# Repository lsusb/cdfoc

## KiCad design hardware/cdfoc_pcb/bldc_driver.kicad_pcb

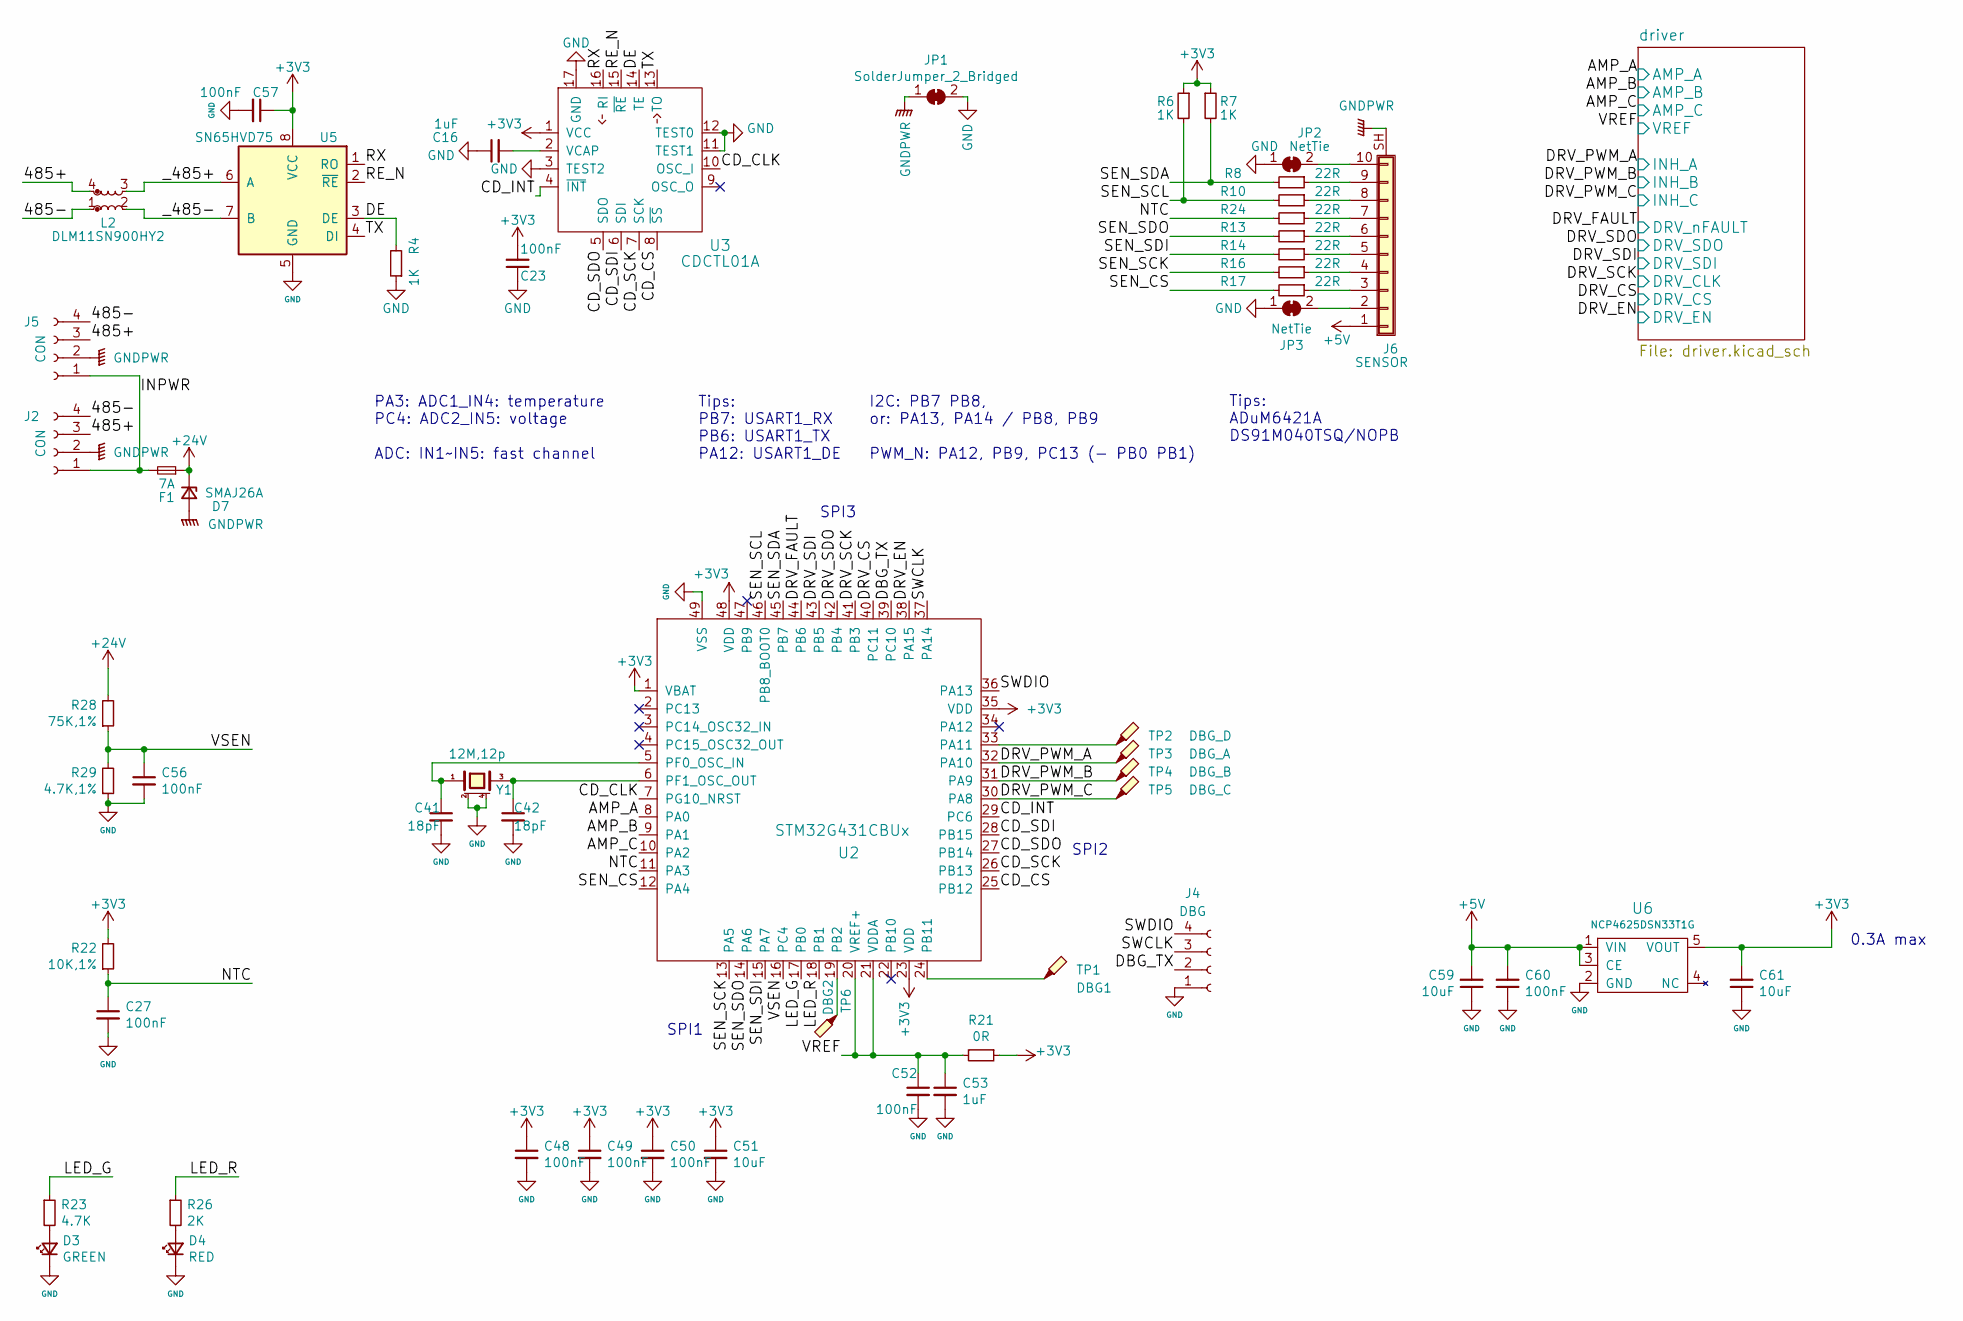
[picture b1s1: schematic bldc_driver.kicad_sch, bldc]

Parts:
C16: 1uF; 0402C_BIG
C23, C27, C48, C49, C50, C52, C56, C57, C60: 100nF; 0402
C41, C42: 18pF; 0402
C51, C59, C61: 10uF; 0402C_BIG
C53: 1uF; 0402
D3: GREEN; 0402D
D4: RED; 0402D
D7: SMAJ26A; SMA
F1: 7A; 1206R
J2, J5: CON; CONN_5268-04A_1x04_P2.50mm_H
J4: DBG; PAD_DIP_4P_1mm
J6: SENSOR; CONN_SH1.0mm_10P_HSMD
JP1: SolderJumper_2_Bridged; NetTie-2_SMD_Pad1mm
JP2, JP3: NetTie; NetTie-2_SMD_Pad0.5mm
L2: DLM11SN900HY2; L_CommonModeChoke_Coilcraft_0603USB
R4, R6, R7: 1K; 0402
R8, R10, R13, R14, R16, R17, R24: 22R; 0402
R21: 0R; 0402
R22: 10K,1%; 0402
R23: 4.7K; 0402
R26: 2K; 0402
R28: 75K,1%; 0402
R29: 4.7K,1%; 0402
TP1: DBG1; TP-D0.8mm
TP2: DBG_D; TP-D0.8mm
TP3: DBG_A; TP-D0.8mm
TP4: DBG_B; TP-D0.8mm
TP5: DBG_C; TP-D0.8mm
TP6: DBG2; TP-D0.8mm
U2: STM32G431CBUx; QFN-48-1EP_7x7mm_P0.5mm_EP5.6x5.6mm
U3: CDCTL01A; QFN-16-1EP_3x3mm_P0.5mm_EP1.7x1.7mm
U5: SN65HVD75; SON-8
U6: NCP4625DSN33T1G; SOT-23-5
Y1: 12M,12p; XTAL-3225

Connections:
+3V3: C23.2, C48.1, C49.1, C50.1, C51.1, C57.1, C61.2, R6.1, R7.1, R21.1, R22.2, U2.1 (VBAT), U2.23 (VDD), U2.35 (VDD), U2.48 (VDD), U3.1 (VCC), U5.8 (VCC), U6.5 (VOUT); also elsewhere on the board
+5V: C59.2, C60.2, J6.1, U6.1 (VIN), U6.3 (CE); also elsewhere on the board
+24V: D7.1 (K), F1.1, R28.2; also elsewhere on the board
/485+: J2.3, J5.3, L2.4
/485-: J2.4, J5.4, L2.1
/AMP_A: U2.8 (PA0); also elsewhere on the board
/AMP_B: U2.9 (PA1); also elsewhere on the board
/AMP_C: U2.10 (PA2); also elsewhere on the board
/CD_CLK: U2.7 (PG10_NRST), U3.10 (OSC_I)
/CD_CS: U2.25 (PB12), U3.8 (~SS)
/CD_INT: U2.29 (PC6), U3.4 (~INT)
/CD_SCK: U2.26 (PB13), U3.7 (SCK)
/CD_SDI: U2.28 (PB15), U3.6 (SDI)
/CD_SDO: U2.27 (PB14), U3.5 (SDO)
/DBG_TX: J4.2, U2.39 (PC10)
/DE: R4.2, U3.14 (TE), U5.3 (DE)
/DRV_CS: U2.40 (PC11); also elsewhere on the board
/DRV_EN: U2.38 (PA15); also elsewhere on the board
/DRV_FAULT: U2.44 (PB6); also elsewhere on the board
/DRV_PWM_A: TP3.1, U2.32 (PA10); also elsewhere on the board
/DRV_PWM_B: TP4.1, U2.31 (PA9); also elsewhere on the board
/DRV_PWM_C: TP5.1, U2.30 (PA8); also elsewhere on the board
/DRV_SCK: U2.41 (PB3); also elsewhere on the board
/DRV_SDI: U2.43 (PB5); also elsewhere on the board
/DRV_SDO: U2.42 (PB4); also elsewhere on the board
/INPWR: F1.2, J2.1, J5.1
/LED_G: R23.1, U2.17 (PB0)
/LED_R: R26.1, U2.18 (PB1)
/NTC: C27.1, R22.1, R24.2, U2.11 (PA3)
/RE_N: U3.15 (~RE), U5.2 (~RE)
/RX: U3.16 (RI), U5.1 (RO)
/SEN_CS: R17.2, U2.12 (PA4)
/SEN_SCK: R16.2, U2.13 (PA5)
/SEN_SCL: R6.2, R10.2, U2.46 (PB8_BOOT0)
/SEN_SDA: R7.2, R8.2, U2.45 (PB7)
/SEN_SDI: R14.2, U2.15 (PA7)
/SEN_SDO: R13.2, U2.14 (PA6)
/SWCLK: J4.3, U2.37 (PA14)
/SWDIO: J4.4, U2.36 (PA13)
/TX: U3.13 (TO), U5.4 (DI)
/VREF: C52.1, C53.1, R21.2, U2.20 (VREF+), U2.21 (VDDA); also elsewhere on the board
/VSEN: C56.1, R28.1, R29.2, U2.16 (PC4)
/_485+: L2.3, U5.6 (A)
/_485-: L2.2, U5.7 (B)
GND: C16.1, C23.1, C27.2, C41.2, C42.2, C48.2, C49.2, C50.2, C51.2, C52.2, C53.2, C56.2, C57.2, C59.1, C60.1, C61.1, D3.1 (K), D4.1 (K), J4.1, JP1.2 (B), JP2.1 (A), JP3.1 (A), R4.1, R29.1, U2.49 (VSS), U3.3 (TEST2), U3.11 (TEST1), U3.12 (TEST0), U3.17 (GND), U5.5 (GND), U6.2 (GND), Y1.2 (case), Y1.4 (case); also elsewhere on the board
GNDPWR: D7.2 (A), J2.2, J5.2, J6.SH (Shield), JP1.1 (A); also elsewhere on the board
unnamed: D3.2 (A), R23.2
unnamed: D4.2 (A), R26.2
unnamed: J6.2, JP3.2 (B)
unnamed: J6.3, R17.1
unnamed: J6.4, R16.1
unnamed: J6.5, R14.1
unnamed: J6.6, R13.1
unnamed: J6.7, R24.1
unnamed: J6.8, R10.1
unnamed: J6.9, R8.1
unnamed: J6.10, JP2.2 (B)
unnamed: TP2.1, U2.33 (PA11)
unnamed: TP6.1, U2.19 (PB2)
unnamed: TP1.1, U2.24 (PB11)
unnamed: C41.1, U2.5 (PF0_OSC_IN), Y1.1
unnamed: C42.1, U2.6 (PF1_OSC_OUT), Y1.3
unnamed: C16.2, U3.2 (VCAP)

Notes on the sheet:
PA3: ADC1_IN4: temperature PC4: ADC2_IN5: voltage ADC: IN1~IN5: fast channel
Tips: PB7: USART1_RX PB6: USART1_TX PA12: USART1_DE
SPI3
SPI1
Tips: ADuM6421A DS91M040TSQ/NOPB
I2C: PB7 PB8, or: PA13, PA14 / PB8, PB9 PWM_N: PA12, PB9, PC13 (- PB0 PB1)
0.3A max
SPI2

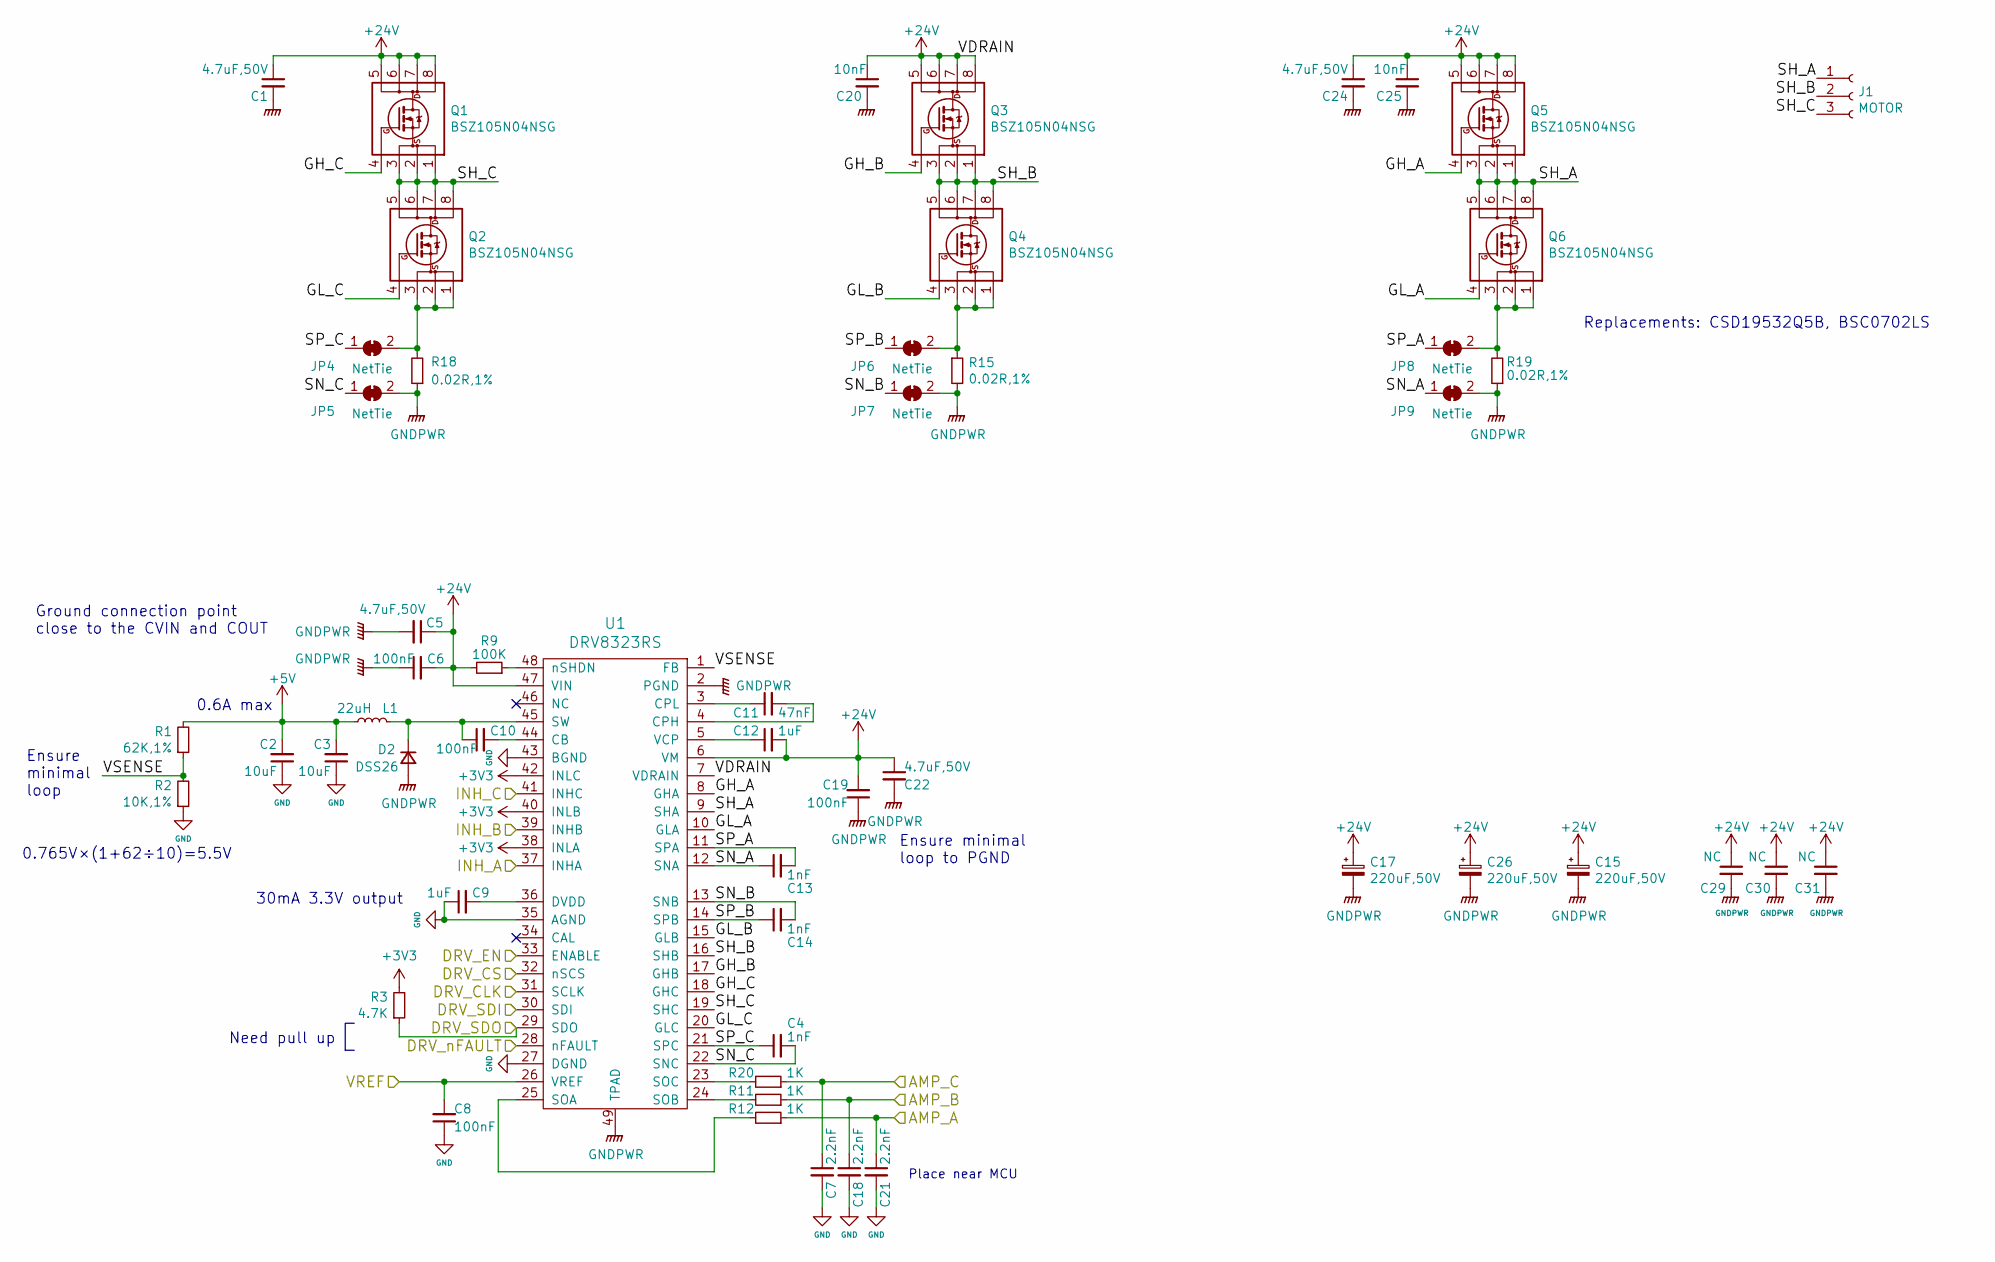
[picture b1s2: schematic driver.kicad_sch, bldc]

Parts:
C1, C5, C22, C24: 4.7uF,50V; 0805
C2, C3: 10uF; 0402C_BIG
C4, C13, C14: 1nF; 0402
C6, C8, C10, C19: 100nF; 0402
C7, C18, C21: 2.2nF; 0402
C9, C12: 1uF; 0402
C11: 47nF; 0402
C15, C17, C26: 220uF,50V; CP_Elec_10x10
C20, C25: 10nF; 0402
C29, C30, C31: NC; 1206
D2: DSS26; D_SOD-123F
J1: MOTOR; CONN_5268-03A_1x03_P2.50mm_H
JP4, JP5, JP6, JP7, JP8, JP9: NetTie; NetTie-2_SMD_Pad0.16mm
L1: 22uH; L_Taiyo-Yuden_MD-4040
Q1, Q2, Q3, Q4, Q5, Q6: BSZ105N04NSG; PG-TSDSON-8_3x3mm
R1: 62K,1%; 0402
R2: 10K,1%; 0402
R3: 4.7K; 0402
R9: 100K; 0402
R11, R12, R20: 1K; 0402
R15, R18, R19: 0.02R,1%; 1206R
U1: DRV8323RS; QFN-48-1EP_7x7mm_P0.5mm_EP5.15x5.15mm

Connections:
+3V3: R3.2, U1.38 (INLA), U1.40 (INLB), U1.42 (INLC); also elsewhere on the board
+5V: C2.2, C3.2, L1.1, R1.2; also elsewhere on the board
+24V: C1.1, C5.1, C6.2, C12.2, C15.1, C17.1, C19.2, C20.1, C22.1, C24.1, C25.1, C26.1, C29.1, C30.1, C31.1, Q1.5 (D), Q1.6 (D), Q1.7 (D), Q1.8 (D), Q3.5 (D), Q3.6 (D), Q3.7 (D), Q3.8 (D), Q5.5 (D), Q5.6 (D), Q5.7 (D), Q5.8 (D), R9.2, U1.6 (VM), U1.7 (VDRAIN), U1.47 (VIN); also elsewhere on the board
/AMP_A: C21.1, R12.1; also elsewhere on the board
/AMP_B: C18.1, R11.1; also elsewhere on the board
/AMP_C: C7.1, R20.1; also elsewhere on the board
/DRV_CS: U1.32 (nSCS); also elsewhere on the board
/DRV_EN: U1.33 (ENABLE); also elsewhere on the board
/DRV_FAULT: U1.28 (nFAULT); also elsewhere on the board
/DRV_PWM_A: U1.37 (INHA); also elsewhere on the board
/DRV_PWM_B: U1.39 (INHB); also elsewhere on the board
/DRV_PWM_C: U1.41 (INHC); also elsewhere on the board
/DRV_SCK: U1.31 (SCLK); also elsewhere on the board
/DRV_SDI: U1.30 (SDI); also elsewhere on the board
/DRV_SDO: R3.1, U1.29 (SDO); also elsewhere on the board
/VREF: C8.2, U1.26 (VREF); also elsewhere on the board
/driver/GH_A: Q5.4 (G), U1.8 (GHA)
/driver/GH_B: Q3.4 (G), U1.17 (GHB)
/driver/GH_C: Q1.4 (G), U1.18 (GHC)
/driver/GL_A: Q6.4 (G), U1.10 (GLA)
/driver/GL_B: Q4.4 (G), U1.15 (GLB)
/driver/GL_C: Q2.4 (G), U1.20 (GLC)
/driver/SH_A: J1.1, Q5.1 (S), Q5.2 (S), Q5.3 (S), Q6.5 (D), Q6.6 (D), Q6.7 (D), Q6.8 (D), U1.9 (SHA)
/driver/SH_B: J1.2, Q3.1 (S), Q3.2 (S), Q3.3 (S), Q4.5 (D), Q4.6 (D), Q4.7 (D), Q4.8 (D), U1.16 (SHB)
/driver/SH_C: J1.3, Q1.1 (S), Q1.2 (S), Q1.3 (S), Q2.5 (D), Q2.6 (D), Q2.7 (D), Q2.8 (D), U1.19 (SHC)
/driver/SN_A: C13.1, JP9.1 (A), U1.12 (SNA)
/driver/SN_B: C14.2, JP7.1 (A), U1.13 (SNB)
/driver/SN_C: C4.2, JP5.1 (A), U1.22 (SNC)
/driver/SP_A: C13.2, JP8.1 (A), U1.11 (SPA)
/driver/SP_B: C14.1, JP6.1 (A), U1.14 (SPB)
/driver/SP_C: C4.1, JP4.1 (A), U1.21 (SPC)
/driver/VSENSE: R1.1, R2.2, U1.1 (FB)
GND: C2.1, C3.1, C7.2, C8.1, C9.1, C18.2, C21.2, R2.1, U1.27 (DGND), U1.35 (AGND), U1.43 (BGND); also elsewhere on the board
GNDPWR: C1.2, C5.2, C6.1, C15.2, C17.2, C19.1, C20.2, C22.2, C24.2, C25.2, C26.2, C29.2, C30.2, C31.2, D2.2 (A), JP5.2 (B), JP7.2 (B), JP9.2 (B), R15.2, R18.1, R19.1, U1.2 (PGND), U1.49 (TPAD); also elsewhere on the board
unnamed: C10.1, D2.1 (K), L1.2, U1.45 (SW)
unnamed: JP4.2 (B), Q2.1 (S), Q2.2 (S), Q2.3 (S), R18.2
unnamed: JP6.2 (B), Q4.1 (S), Q4.2 (S), Q4.3 (S), R15.1
unnamed: JP8.2 (B), Q6.1 (S), Q6.2 (S), Q6.3 (S), R19.2
unnamed: C10.2, U1.44 (CB)
unnamed: C11.2, U1.4 (CPH)
unnamed: C11.1, U1.3 (CPL)
unnamed: C9.2, U1.36 (DVDD)
unnamed: R12.2, U1.25 (SOA)
unnamed: R11.2, U1.24 (SOB)
unnamed: R20.2, U1.23 (SOC)
unnamed: C12.1, U1.5 (VCP)
unnamed: R9.1, U1.48 (nSHDN)

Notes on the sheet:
Ground connection point close to the CVIN and COUT
Need pull up
Replacements: CSD19532Q5B, BSC0702LS
30mA 3.3V output
Ensure minimal loop to PGND
0.765V×(1+62÷10)=5.5V
0.6A max
Place near MCU
Ensure minimal loop

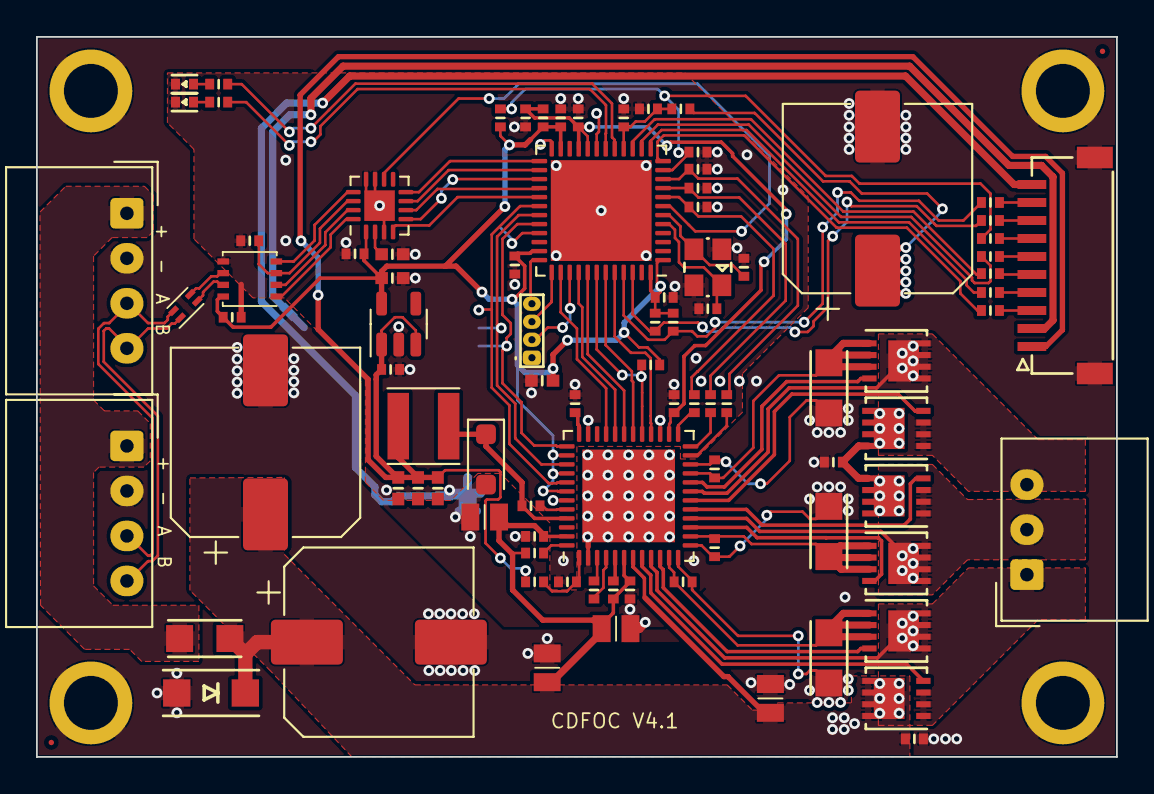
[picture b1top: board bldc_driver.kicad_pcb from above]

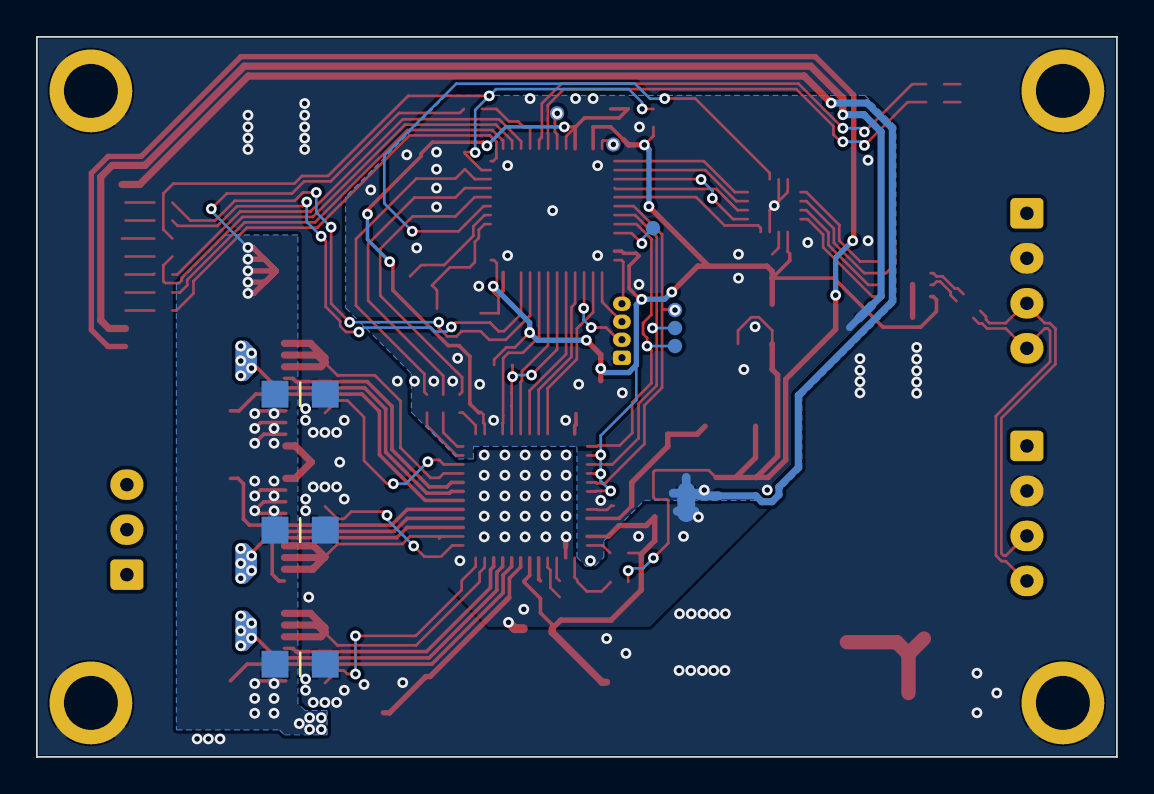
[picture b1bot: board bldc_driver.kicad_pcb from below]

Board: 2 copper layers, 60.0 x 40.0 mm, 112 parts (12 on the bottom side), 92 nets.

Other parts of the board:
J11, J12, J13, J14: Hole; Hole-TH-3.2mm_4mm

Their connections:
GNDPWR: J11.1, J12.1, J13.1, J14.1; also elsewhere on the board

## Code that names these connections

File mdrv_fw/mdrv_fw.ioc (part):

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Mcu.Name=STM32G431C(6-8-B)Ux
Mcu.Package=UFQFPN48
Mcu.UserName=STM32G431CBUx
PA0.Signal=SharedAnalog_PA0
PA1.Signal=SharedAnalog_PA1
PA10.GPIOParameters=GPIO_Speed
PA10.GPIO_Speed=GPIO_SPEED_FREQ_HIGH
PA10.Signal=S_TIM1_CH3
PA11.GPIOParameters=GPIO_Speed
PA11.GPIO_Speed=GPIO_SPEED_FREQ_HIGH
PA11.Signal=S_TIM1_CH4
PA13.Mode=Serial_Wire
PA13.Signal=SYS_JTMS-SWDIO
PA14.Mode=Serial_Wire
PA14.Signal=SYS_JTCK-SWCLK
PA15.GPIOParameters=GPIO_Speed,GPIO_Label
PA15.GPIO_Label=DRV_EN
PA15.GPIO_Speed=GPIO_SPEED_FREQ_HIGH
PA15.Signal=GPIO_Output
PA2.Mode=IN3-Single-Ended
PA2.Signal=ADC1_IN3
PA3.Mode=IN4-Single-Ended
PA3.Signal=ADC1_IN4
PA4.GPIOParameters=GPIO_Speed,PinState,GPIO_Label
PA4.GPIO_Label=SEN_CS
PA4.GPIO_Speed=GPIO_SPEED_FREQ_HIGH
PA4.PinState=GPIO_PIN_SET
PA4.Signal=GPIO_Output
PA5.GPIOParameters=GPIO_Speed
PA5.GPIO_Speed=GPIO_SPEED_FREQ_HIGH
PA5.Mode=Full_Duplex_Master
PA5.Signal=SPI1_SCK
PA6.GPIOParameters=GPIO_Speed,GPIO_PuPd
PA6.GPIO_PuPd=GPIO_NOPULL
PA6.GPIO_Speed=GPIO_SPEED_FREQ_HIGH
PA6.Mode=Full_Duplex_Master
PA6.Signal=SPI1_MISO
PA7.GPIOParameters=GPIO_Speed
PA7.GPIO_Speed=GPIO_SPEED_FREQ_HIGH
PA7.Mode=Full_Duplex_Master
PA7.Signal=SPI1_MOSI
PA8.GPIOParameters=GPIO_Speed
PA8.GPIO_Speed=GPIO_SPEED_FREQ_HIGH
PA8.Signal=S_TIM1_CH1
PA9.GPIOParameters=GPIO_Speed
PA9.GPIO_Speed=GPIO_SPEED_FREQ_HIGH
PA9.Signal=S_TIM1_CH2
PB0.GPIOParameters=GPIO_Label
PB0.GPIO_Label=LED_G
PB0.Signal=GPIO_Output
PB1.GPIOParameters=GPIO_Label
PB1.GPIO_Label=LED_R
PB1.Signal=GPIO_Output
PB11.GPIOParameters=GPIO_Speed,GPIO_Label
PB11.GPIO_Label=DBG_OUT1
PB11.GPIO_Speed=GPIO_SPEED_FREQ_HIGH
PB11.Signal=GPIO_Output
PB12.GPIOParameters=GPIO_Speed,PinState,GPIO_Label
PB12.GPIO_Label=CD_CS
PB12.GPIO_Speed=GPIO_SPEED_FREQ_HIGH
PB12.PinState=GPIO_PIN_SET
PB12.Signal=GPIO_Output
PB13.GPIOParameters=GPIO_Speed
PB13.GPIO_Speed=GPIO_SPEED_FREQ_HIGH
PB13.Mode=Full_Duplex_Master
PB13.Signal=SPI2_SCK
PB14.GPIOParameters=GPIO_Speed
PB14.GPIO_Speed=GPIO_SPEED_FREQ_HIGH
PB14.Mode=Full_Duplex_Master
PB14.Signal=SPI2_MISO
PB15.GPIOParameters=GPIO_Speed
PB15.GPIO_Speed=GPIO_SPEED_FREQ_HIGH
PB15.Mode=Full_Duplex_Master
PB15.Signal=SPI2_MOSI
PB2.GPIOParameters=GPIO_Speed,GPIO_Label
PB2.GPIO_Label=DBG_OUT2
PB2.GPIO_Speed=GPIO_SPEED_FREQ_HIGH
PB2.Signal=GPIO_Output
PB3.GPIOParameters=GPIO_Speed
PB3.GPIO_Speed=GPIO_SPEED_FREQ_MEDIUM
PB3.Mode=Full_Duplex_Master
PB3.Signal=SPI3_SCK
PB4.GPIOParameters=GPIO_Speed,GPIO_PuPd
PB4.GPIO_PuPd=GPIO_PULLUP
PB4.GPIO_Speed=GPIO_SPEED_FREQ_MEDIUM
PB4.Mode=Full_Duplex_Master
PB4.Signal=SPI3_MISO
PB5.GPIOParameters=GPIO_Speed
PB5.GPIO_Speed=GPIO_SPEED_FREQ_MEDIUM
PB5.Mode=Full_Duplex_Master
PB5.Signal=SPI3_MOSI
PB6.GPIOParameters=GPIO_PuPd,GPIO_Label
PB6.GPIO_Label=DRV_FAULT
PB6.GPIO_PuPd=GPIO_PULLUP
PB6.Signal=GPIO_Input
PB7.GPIOParameters=GPIO_Pu
PB7.GPIO_Pu=GPIO_PULLUP
PB7.Mode=I2C
PB7.Signal=I2C1_SDA
PB8-BOOT0.GPIOParameters=GPIO_Pu
PB8-BOOT0.GPIO_Pu=GPIO_PULLUP
PB8-BOOT0.Mode=I2C
PB8-BOOT0.Signal=I2C1_SCL
PC10.GPIOParameters=GPIO_PuPd
PC10.GPIO_PuPd=GPIO_PULLUP
PC10.Mode=Half_duplex(single_wire_mode)
PC10.Signal=USART3_TX
PC11.GPIOParameters=GPIO_Speed,PinState,GPIO_Label
PC11.GPIO_Label=DRV_CS
PC11.GPIO_Speed=GPIO_SPEED_FREQ_MEDIUM
PC11.PinState=GPIO_PIN_SET
PC11.Signal=GPIO_Output
PC4.Mode=IN5-Single-Ended
PC4.Signal=ADC2_IN5
PC6.GPIOParameters=GPIO_PuPd,GPIO_Label,GPIO_ModeDefaultEXTI
PC6.GPIO_Label=CD_INT
PC6.GPIO_ModeDefaultEXTI=GPIO_MODE_IT_FALLING
PC6.GPIO_PuPd=GPIO_PULLUP
PC6.Signal=GPXTI6
PF0-OSC_IN.Mode=HSE-External-Oscillator
PF0-OSC_IN.Signal=RCC_OSC_IN
PF1-OSC_OUT.Mode=HSE-External-Oscillator
PF1-OSC_OUT.Signal=RCC_OSC_OUT
PG10-NRST.GPIOParameters=GPIO_Speed
PG10-NRST.GPIO_Speed=GPIO_SPEED_FREQ_MEDIUM
PG10-NRST.Mode=Clock-out
PG10-NRST.Signal=RCC_MCO
RCC.HSE_VALUE=12000000
RCC.SYSCLKFreq_VALUE=170000000
RCC.SYSCLKSource=RCC_SYSCLKSOURCE_PLLCLK
board=custom

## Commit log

2024-01-15 st_foc
2024-01-16 添加文件
2024-01-17 开环给Vqd测试
2024-01-17 ams5311测试中
2024-01-17 as5311读取成功
2024-01-17 30k读取频率
2024-01-18 电角度解算+无电流环运行测试
